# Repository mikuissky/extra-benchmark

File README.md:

# extra-benchmark
The extra benchmarks of paper "ADSAPlace:Alignment-Driven Simulated  Annealing for PCB Placement"

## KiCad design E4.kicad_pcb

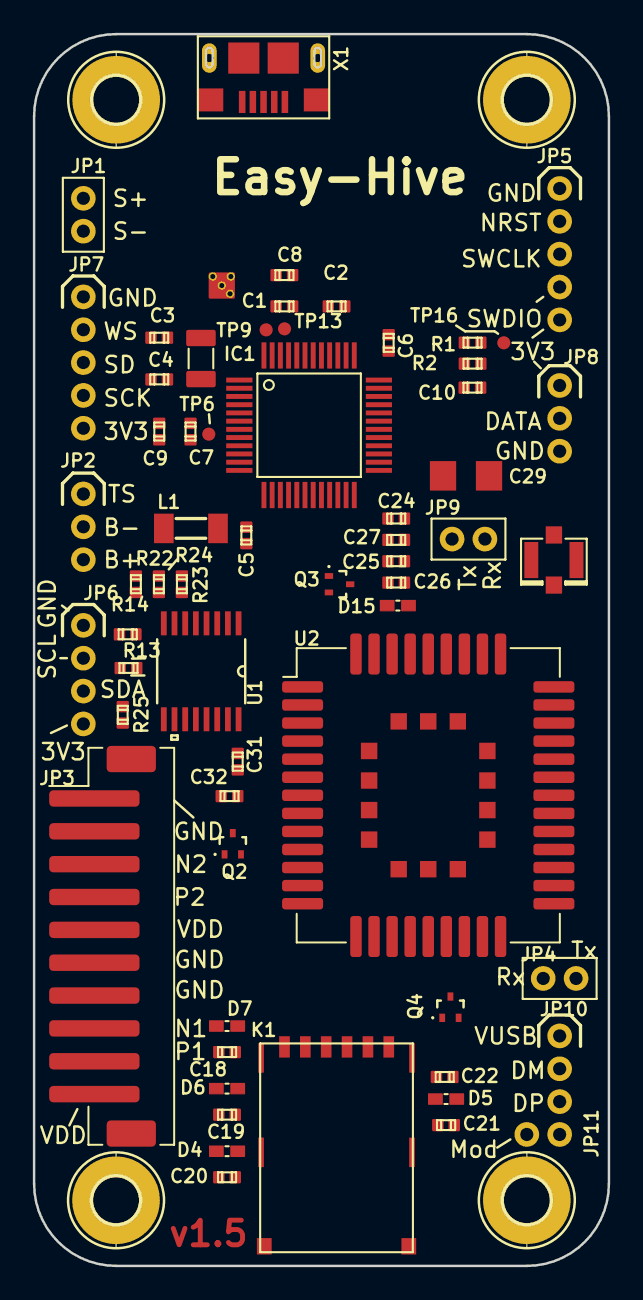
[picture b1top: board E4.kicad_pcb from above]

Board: 2 copper layers, 35.0 x 75.0 mm, 106 parts (0 on the bottom side), 82 nets, no tracks yet.

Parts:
C1, C5, C6, C7, C14, C15, C24, C28: 100n; C0402
C2, C11, C30, C31, C32: 1u; C0402
C3, C4, C26: 15p; C0402
C8, C9, C16, C17: 10u; C0402
C10: 100p; C0402
C12, C13, C23: 4u7; C0402
C18, C19, C20, C21: 47p; C0402
C22: 100nF; C0402
C25: 56p; C0402
C27: 10n; C0402
C29: 100u; 1206
D1, D2: MBR0520LT; SOD123
D4, D5, D6, D7, D8, D9, D10, D11, D12, D13, D14, D15: PESD0402-140; 0402-TVS
F1: 6V/0.5A; 1206
H1, H2, H3, H4: MOUNT-PAD-ROUND2.8; 2,8-PAD
IC1: ATSAMD21G; TQFP48
IC2: BQ2407X; VQFN16
IC3: ADS1232; TSSOP24
IC4: DS18B20U; UMAX8
IC5: XC6220B331; SOT25
IC7: TPS22919; sot-sc70-6
J1: U.FL
JP1: Solar; 1X02_2MM_klein
JP2: Battery; 1X03-2MM_klein
JP3: JST PH; JST_PH_B10B-PH-SM4-TB_1x10-1MP_P2.00mm_Vertical
JP4: UART_AUX; 1X02_2MM_klein
JP5: SWD; 1X05-2MM_klein
JP6: I2C; 1X04-2MM_klein
JP7: I2S; 1X05-2MM_klein
JP8: ext. DS18B20; 1X03-2MM_re_klein
JP9: UART_DBG; 1X02_2MM_klein
JP10: USB_BC66; 1X03-2MM_klein
JP11: USB_MODE; 1X02_2MM_klein
K1: 693043020611
L1, L2: SM-1206
P1: PKMCS; PKMCS_BUZZER
Q1: 32768 Hz; FC135
Q2, Q3, Q4: DTC123JET1G; SC75_SOT416
R1: 330; C0402
R2: 2k2; C0402
R3, R22, R23, R24: 0R; C0402
R4: 1k18; C0402
R5: 680R; C0402
R6, R10: 10K; C0402
R7, R8, R9: 22R; C0402
R13, R14: 2k; C0402
R15: NTC 103AT; C0402
R16: 4M7; C0402
R17: 10M; C0402
R18: 4k7; C0402
R25: 1M; C0402
TP6, TP9, TP10, TP11, TP13, TP16: TPTP08R; TP08R
U1: SN74AVC4T774PWG4; PW16
U2: BC66; Quectel_BC66
X1: USB_MICRO_SHIELD; USBMICRO

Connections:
+3V3: C1.1, C5.1, C6.1, C8.1, C10.1, C17.1, C24.1, C25.1, C26.1, C27.1, C29.1, C30.1, C31.2, D14.P$2, D15.P$2, IC1.17, IC1.36, IC1.44, IC3.1, IC3.19, IC3.20, IC4.8, IC5.5, IC7.1, JP5.5, JP6.4, JP7.5, JP8.3, L1.2, R2.2, R13.2, R14.2, R18.2, R24.1, R25.2, TP10.TP, U1.16, U2.42, U2.43
/3V3_LC: C15.1, IC3.16, IC3.18, IC7.4, JP3.5, JP3.10
/+1V8: C32.2, U1.15, U2.24
/ADS_A0: IC1.28, IC3.8
/AIN0: C28.1, IC1.3, R16.1, R17.2
/BC66_1V8_ENABLE: IC1.25, R25.1, U1.9
/BC66_PSM: IC1.8, Q4.1
/BC66_PWRON: IC1.19, Q2.1
/BC66_RI_1V8: U1.13, U2.20
/BC66_RI_3V3: IC1.23, U1.4
/BC66_RST: IC1.20, Q3.1
/BC66_RXD_1V8: U1.11, U2.18
/BC66_RXD_3V3: IC1.21, U1.6
/BC66_TXD_1V8: U1.12, U2.17
/BC66_TXD_3V3: IC1.22, U1.5
/BUZZER: IC1.41, P1.1
/DATA: IC1.10, IC3.24
/DS_DATA: IC1.39, IC4.1, JP8.2, R18.1, TP11.TP
/I2S_SCK: IC1.15, JP7.4
/I2S_SD: IC1.13, JP7.3
/I2S_WS: IC1.16, JP7.2
/LC_ON: IC1.29, IC7.3
/PB02: IC1.47, TP13.TP
/PB03: IC1.48, TP9.TP
/PB08: IC1.7, TP6.TP
/PDWN: IC1.12, IC3.22
/SAM_SCL: IC1.32, JP6.2, R14.1
/SAM_SDA: IC1.31, JP6.3, R13.1
/SCLK: IC1.11, IC3.23
/SWCLK: D12.P$2, IC1.45, JP5.3
/SWDIO: D13.P$2, IC1.46, JP5.4
/TEMP_EN: IC1.9, IC3.7
/USBN: D9.P$2, IC1.33, X1.2
/USBP: D8.P$2, IC1.34, X1.3
/VBAT: C12.1, IC2.2, IC2.3, JP2.3, R16.2
/VUSB: C23.1, D2.A, L2.2
/~RESET: C10.2, D11.P$2, IC1.40, JP5.2, R1.2, R2.1
GND: C1.2, C2.2, C3.2, C4.2, C5.2, C6.2, C7.2, C8.2, C9.2, C11.2, C12.2, C13.2, C15.2, C16.2, C17.2, C18.2, C19.2, C20.2, C21.2, C22.1, C23.2, C24.2, C25.2, C26.2, C27.2, C28.2, C29.2, C30.2, C31.1, C32.1, D4.P$2, D5.P$2, D6.P$2, D7.P$2, D8.P$1, D9.P$1, D10.P$1, D11.P$1, D12.P$1, D13.P$1, D14.P$1, D15.P$1, H1.B2,8, H2.B2,8, H3.B2,8, H4.B2,8, IC1.5, IC1.18, IC1.35, IC1.42, IC2.4, IC2.6, IC2.8, IC2.15, IC3.2, IC3.3, IC3.5, IC3.6, IC3.15, IC3.17, IC3.21, IC4.4, IC5.2, IC7.2, J1.P$1, J1.P$2, JP1.1, JP2.2, JP3.1, JP3.2, JP3.6, JP3.7, JP5.1, JP6.1, JP7.1, JP8.1, JP11.2, K1.C5, K1.Z1, K1.Z2, K1.Z3, K1.Z4, K1.Z5, K1.Z6, P1.2, Q2.2, Q3.2, Q4.2, R3.1, R4.1, R5.1, R15.1, R17.1, R22.1, R23.1, U1.10, U2.1, U2.10, U2.27, U2.34, U2.36, U2.37, U2.40, U2.41, X1.5, X1.S1, X1.S2, X1.S3, X1.S4, X1.S5, X1.S6
unnamed: C2.1, IC1.43
unnamed: C3.1, IC1.1, Q1.1
unnamed: C4.1, IC1.2, Q1.2
unnamed: C7.1, C9.1, IC1.6, L1.1
unnamed: C11.1, D1.C, D2.C, IC2.13
unnamed: C13.1, F1.1, IC2.5, IC2.10, IC2.11
unnamed: C14.1, IC3.9
unnamed: C14.2, IC3.10
unnamed: C18.1, D7.P$1, K1.C7, R8.2
unnamed: C19.1, D6.P$1, K1.C3, R9.2
unnamed: C20.1, D4.P$1, K1.C2, R7.2
unnamed: C21.1, C22.2, D5.P$1, K1.C1, R6.1, U2.14
unnamed: D1.A, JP1.2
unnamed: D10.P$2, L2.1, X1.1
unnamed: IC2.1, JP2.1, R15.2
unnamed: IC2.12, R4.2
unnamed: IC2.14, R3.2
unnamed: IC2.16, R5.2
unnamed: IC2.17, IC2.V1, IC2.V2, IC2.V3, IC2.V4
unnamed: IC3.11, JP3.9
unnamed: IC3.12, JP3.8
unnamed: IC3.13, JP3.3
unnamed: IC3.14, JP3.4
unnamed: J1.P$3, U2.35
unnamed: JP4.1, U2.29
unnamed: JP4.2, U2.28
unnamed: JP9.1, U2.39
unnamed: JP9.2, U2.38
unnamed: JP10.1, U2.49
unnamed: JP10.2, U2.51
unnamed: JP10.3, U2.50
unnamed: JP11.1, R10.2
unnamed: Q2.3, U2.7
unnamed: Q3.3, U2.15
unnamed: Q4.3, U2.19
unnamed: R1.1, TP16.TP
unnamed: R6.2, R8.1, U2.11
unnamed: R7.1, U2.12
unnamed: R9.1, U2.13
unnamed: R10.1, U2.47
unnamed: R22.2, U1.2
unnamed: R23.2, U1.7
unnamed: R24.2, U1.8
VCC: C16.1, F1.2, IC5.1, IC5.3

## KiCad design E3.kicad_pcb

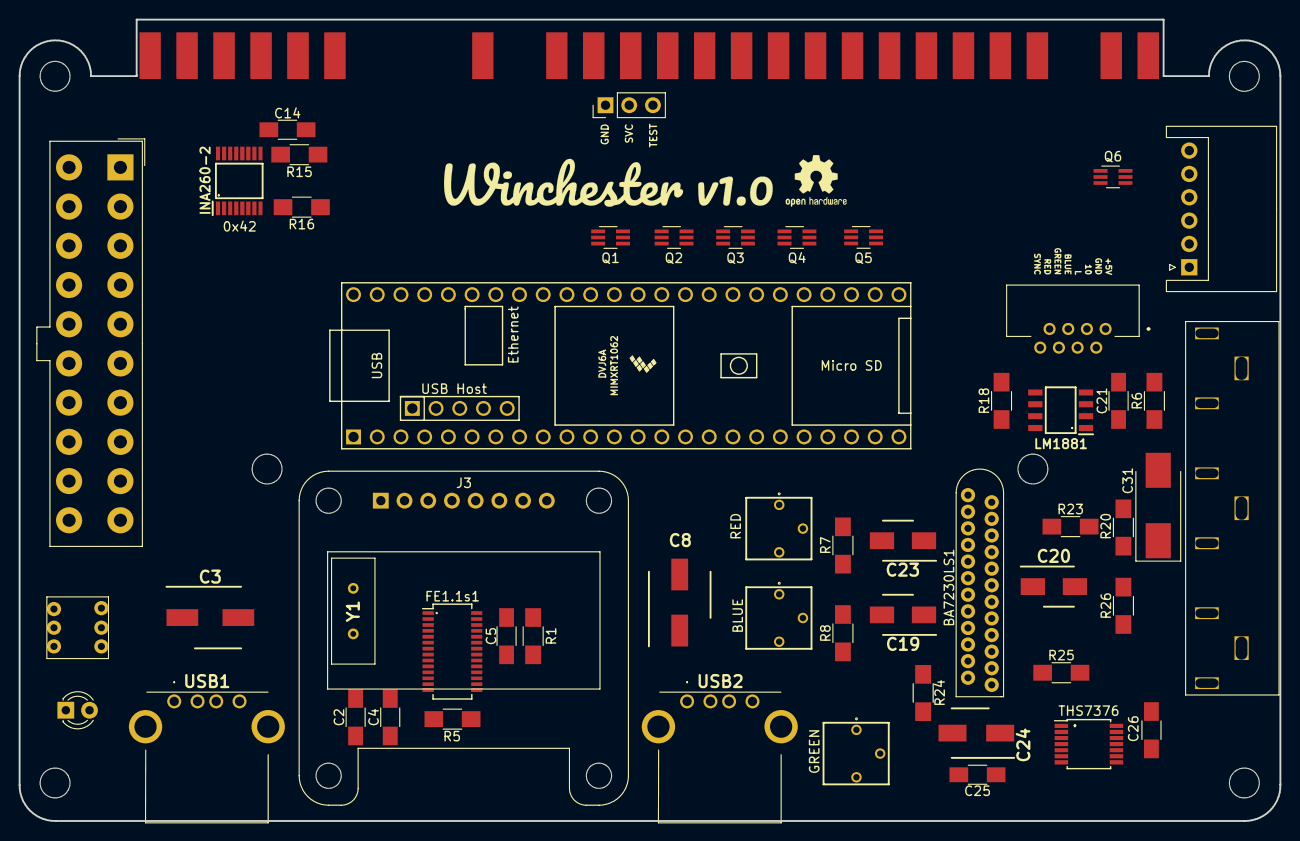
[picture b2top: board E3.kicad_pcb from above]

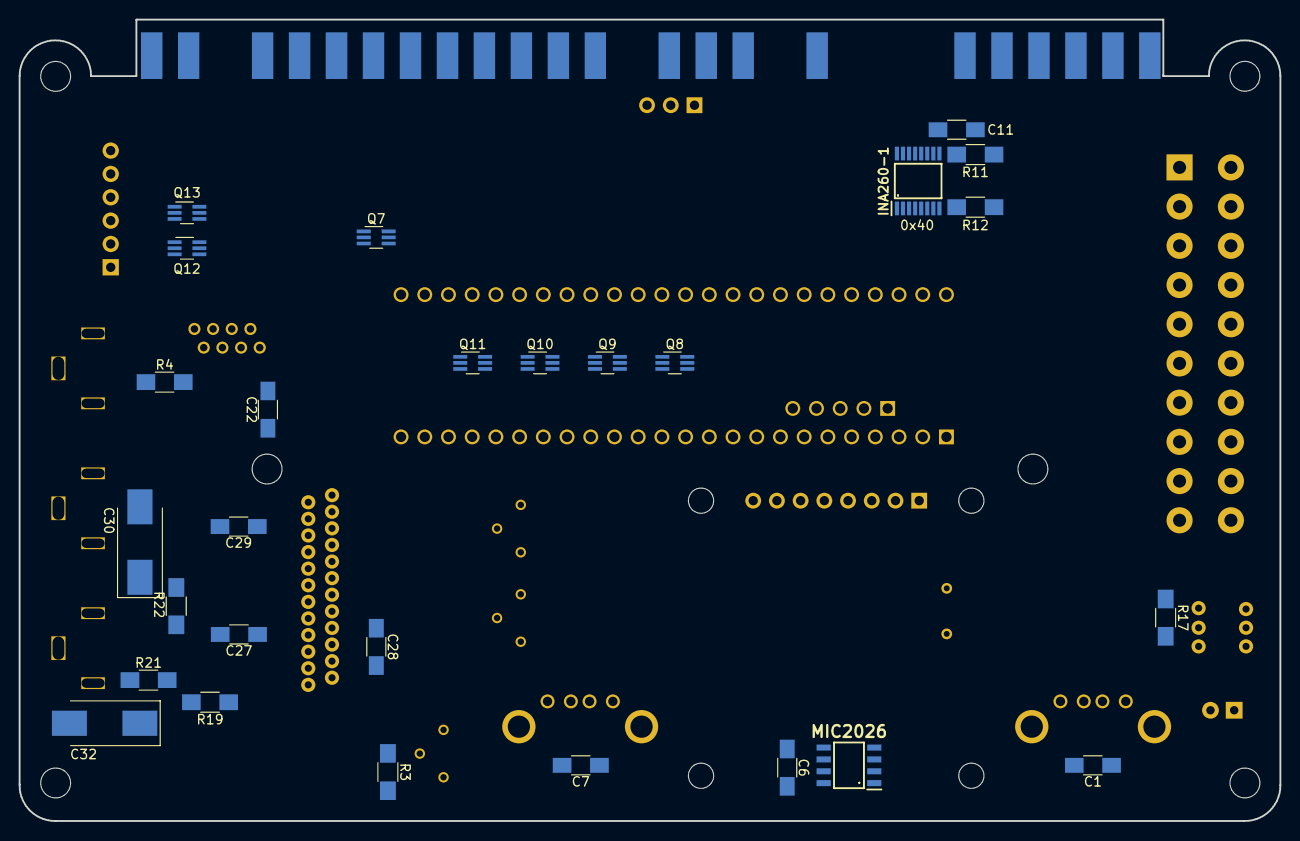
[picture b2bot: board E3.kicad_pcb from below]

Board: 2 copper layers, 135.1 x 85.8 mm, 89 parts (27 on the bottom side), 117 nets, no tracks yet.

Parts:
ATX1: ATX20; Molex_MiniFit-JR-5556-20A_2x10x4.20mm_Straight
BA7230LS1: BA7230LS; szip24
B_POT1: R_POT_TRIM; 3362P_1
C1, C6, C7, C21, C22, C26, C27, C28, C29: 0.1uF; C_1206_HandSoldering
C2, C4, C5: 10uF; C_1206_HandSoldering
C3, C8: 220uF; EEE-1CA221XP
C11, C14: 1uF; C_1206_HandSoldering
C19, C20, C23: 1uF; EEE1HA010SR
C24: 10uF; EEE-1EA100SR
C25: 0.047uF; C_1206_HandSoldering
C30, C31, C32: 220uF; CP_Tantalum_Case-D_EIA-7343-31_Hand
COMPONENT1: PJRAN
D1: LED; LED_D3.0mm
FE1.1s1: FE1.1s; SSOP-28_3.9x9.9mm_Pitch0.635mm
G_POT1: R_POT_TRIM; 3362P_1
H1, H2, H3, H4, H5, H6: MountingHole; MountingHole_3.2mm_M3
INA260-1, INA260-2: INA260
J1: Conn_01x03_Female; Pin_Header_Straight_1x03_Pitch2.54mm
J2: SLW8R-5C7LF; SLW8R5C7LF
J3: SSD1306 OLED; Adafruit_SSD1306
KICK1: JST-XH; JST_XH_S06B-XH-A_06x2.50mm_Angled
L1: Logo; v1
LM1881: LM1881
LOGO1: Logo_Open_Hardware_Small; OSHW-Logo2_7.3x6mm_SilkScreen
MIC2026: MIC2026-2YM; SOIC127P599X173-8N
POWER1: SW_DPDT_x2; POWER_SW
Q1, Q2, Q3, Q4, Q5, Q6, Q7, Q8, Q9, Q10, Q11, Q12, Q13: MUN5230DW1T1G; SOT-363_SC-70-6_Handsoldering
R1, R11, R12, R15, R16: 10k; R_1206_HandSoldering
R3, R6, R7, R8: 390ohm; R_1206_HandSoldering
R4: 1Kohm; R_1206_HandSoldering
R5: 2.7k; R_1206_HandSoldering
R17: 330; R_1206_HandSoldering
R18: 680k; R_1206_HandSoldering
R19: 82ohm; R_1206_HandSoldering
R20: 56ohm; R_1206_HandSoldering
R21: 91ohm; R_1206_HandSoldering
R22: 75ohm; R_1206_HandSoldering
R23, R24, R25: 3.6Mohm; R_1206_HandSoldering
R26: 200ohm; R_1206_HandSoldering
R_POT1: R_POT_TRIM; 3362P_1
THS7376: THS7376; TSSOP-14_4.4x5mm_Pitch0.65mm
U1: Jamma; JAMMA56HALF
U7: Teensy4.1; Teensy41
USB1, USB2: USB_A; 875201010BLF
Y1: ECS120; ECS120184XCKM

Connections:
+3V3: ATX1.11, R1.1
+5V: ATX1.19, ATX1.20, BA7230LS1.24, C5.2, C6.2, C11.1, C14.1, C24.1, C25.1, C26.1, FE1.1s1.20, INA260-1.10, INA260-2.10, J2.1, J3.7, LM1881.8, MIC2026.7, R11.1, R12.1, R15.1, R16.1, R23.1, R24.1, R25.1, THS7376.10, U7.48
-5V: ATX1.18, U1.5, U1.E
/10: J2.3, U1.10
/+5VA: ATX1.4, ATX1.6, INA260-2.1, INA260-2.2, INA260-2.3, INA260-2.12
/+5VB: INA260-2.14, INA260-2.15, INA260-2.16, U1.3, U1.4, U1.C, U1.D
/+12VA: ATX1.10, INA260-1.1, INA260-1.2, INA260-1.3, INA260-1.12
/+12VB: INA260-1.14, INA260-1.15, INA260-1.16, U1.6, U1.F
/B: B_POT1.1, U1.13
/B-Y: C28.2, R24.2, THS7376.3
/BLUE: B_POT1.2, C19.2, J2.5, R8.2
/BYPASS: THS7376.9, U7.17
/CH1: C30.2, COMPONENT1.6, COMPONENT1.7
/CH2: C31.2, COMPONENT1.8, COMPONENT1.9
/CH3: C32.2, COMPONENT1.4, COMPONENT1.5
/COIN_P1: Q1.3, U1.16
/COIN_P2: Q8.6, U1.T
/CSYNC: J2.8, LM1881.1, R26.2
/DM: FE1.1s1.15, U7.56
/DM1: FE1.1s1.10, USB1.2
/DM2: FE1.1s1.8, USB2.2
/DP: FE1.1s1.16, U7.57
/DP1: FE1.1s1.11, USB1.3
/DP2: FE1.1s1.9, USB2.3
/ENP: FE1.1s1.25, MIC2026.1, MIC2026.4
/G: G_POT1.1, U1.N
/GREEN: C20.2, G_POT1.2, J2.6, R3.1
/L: J2.4, U1.L
/OVCJ: FE1.1s1.26, MIC2026.2, MIC2026.3, R1.2
/P1_B1: Q4.3, U1.22
/P1_B1_29: Q4.5, U7.29
/P1_B2: Q4.6, U1.23
/P1_B2_30: Q4.2, U7.30
/P1_B3: Q5.3, U1.24
/P1_B3_27: Q5.5, U7.27
/P1_B4: KICK1.1, Q12.3
/P1_B4_23: Q12.5, U7.23
/P1_B4_28: Q5.2, U7.28
/P1_B4_N: Q5.6, U1.25
/P1_B5: KICK1.3, Q13.3
/P1_B5_21: Q13.5, U7.21
/P1_B6: KICK1.5, Q6.6
/P1_B6_19: Q6.2, U7.19
/P1_COIN_37: Q1.5, U7.37
/P1_DOWN: Q2.6, U1.19
/P1_DOWN_36: Q2.2, U7.36
/P1_LEFT: Q3.3, U1.20
/P1_LEFT_32: Q3.5, U7.32
/P1_RIGHT: Q3.6, U1.21
/P1_RIGHT_33: Q3.2, U7.33
/P1_START: Q1.6, U1.17
/P1_START_38: Q1.2, U7.38
/P1_UP: Q2.3, U1.18
/P1_UP_35: Q2.5, U7.35
/P2_B1: Q11.6, U1.Z
/P2_B1_18: Q11.2, U7.18
/P2_B2: Q11.3, U1._a
/P2_B2_14: Q11.5, U7.14
/P2_B3: Q7.6, U1._b
/P2_B3_25: Q7.2, U7.25
/P2_B4: KICK1.2, Q12.6
/P2_B4_24: Q12.2, U7.24
/P2_B4_26: Q7.5, U7.26
/P2_B4_N: Q7.3, U1._c
/P2_B5: KICK1.4, Q13.6
/P2_B5_22: Q13.2, U7.22
/P2_B6: KICK1.6, Q6.3
/P2_B6_20: Q6.5, U7.20
/P2_COIN_9: Q8.2, U7.9
/P2_DOWN: Q9.3, U1.W
/P2_DOWN_10: Q9.5, U7.10
/P2_LEFT: Q10.6, U1.X
/P2_LEFT_13: Q10.2, U7.13
/P2_RIGHT: Q10.3, U1.Y
/P2_RIGHT_12: Q10.5, U7.12
/P2_START: Q8.3, U1.U
/P2_START_8: Q8.5, U7.8
/P2_UP: Q9.6, U1.V
/P2_UP_11: Q9.2, U7.11
/R: R_POT1.1, U1.12
/R-Y: C27.2, R25.2, THS7376.4
/RED: C23.2, J2.7, R7.2, R_POT1.2
/S: R4.2, U1.P
/SCL: INA260-1.9, INA260-2.9, J3.2, R11.2, R15.2, U7.41
/SDA: INA260-1.5, INA260-1.8, INA260-2.8, J3.1, R12.2, R16.2, U7.40
/SERVICE: J1.2, U1.R
/SYNC: C21.2, R4.1, R6.2
/TEST: J1.3, U1.15
/USBA5V: C1.1, C3.1, MIC2026.8, USB1.1
/USBB5V: C7.1, C8.1, MIC2026.5, USB2.1
/USBVCC: FE1.1s1.18, U7.55
/Y: C29.2, R23.2, THS7376.2
GND: ATX1.3, ATX1.5, ATX1.7, ATX1.13, ATX1.16, ATX1.17, BA7230LS1.19, B_POT1.3, C1.2, C2.1, C3.2, C4.1, C5.1, C6.1, C7.2, C8.2, C11.2, C14.2, C22.1, C24.2, C25.2, C26.2, COMPONENT1.1, COMPONENT1.2, COMPONENT1.3, D1.1, FE1.1s1.1, G_POT1.3, INA260-1.4, INA260-1.6, INA260-1.11, INA260-2.4, INA260-2.5, INA260-2.6, INA260-2.11, J1.1, J2.2, J3.8, LM1881.4, MIC2026.6, Q1.1, Q1.4, Q2.1, Q2.4, Q3.1, Q3.4, Q4.1, Q4.4, Q5.1, Q5.4, Q6.1, Q6.4, Q7.1, Q7.4, Q8.1, Q8.4, Q9.1, Q9.4, Q10.1, Q10.4, Q11.1, Q11.4, Q12.1, Q12.4, Q13.1, Q13.4, R3.2, R5.2, R6.1, R7.1, R8.1, R18.1, R_POT1.3, THS7376.5, THS7376.6, U1.1, U1.2, U1.14, U1.27, U1.28, U1.A, U1.B, U1._e, U1._f, U7.1, U7.34, U7.47, U7.58, U7.59, USB1.4, USB2.4
unnamed: ATX1.8, R17.1
unnamed: ATX1.14, POWER1.3
unnamed: ATX1.15, POWER1.1
unnamed: BA7230LS1.13, C23.1
unnamed: BA7230LS1.14, C20.1
unnamed: BA7230LS1.15, C19.1
unnamed: BA7230LS1.16, C29.1
unnamed: BA7230LS1.17, C28.1
unnamed: BA7230LS1.18, C27.1
unnamed: C2.2, FE1.1s1.12, FE1.1s1.28
unnamed: C4.2, FE1.1s1.13, FE1.1s1.19, FE1.1s1.21
unnamed: C21.1, LM1881.2
unnamed: C22.2, LM1881.6, R18.2
unnamed: C30.1, R22.1
unnamed: C31.1, R20.1
unnamed: C32.1, R21.1
unnamed: D1.2, R17.2
unnamed: FE1.1s1.2, Y1.2
unnamed: FE1.1s1.3, Y1.1
unnamed: FE1.1s1.14, R5.1
unnamed: R19.1, R22.2, R26.1
unnamed: R19.2, THS7376.13
unnamed: R20.2, THS7376.12
unnamed: R21.2, THS7376.11

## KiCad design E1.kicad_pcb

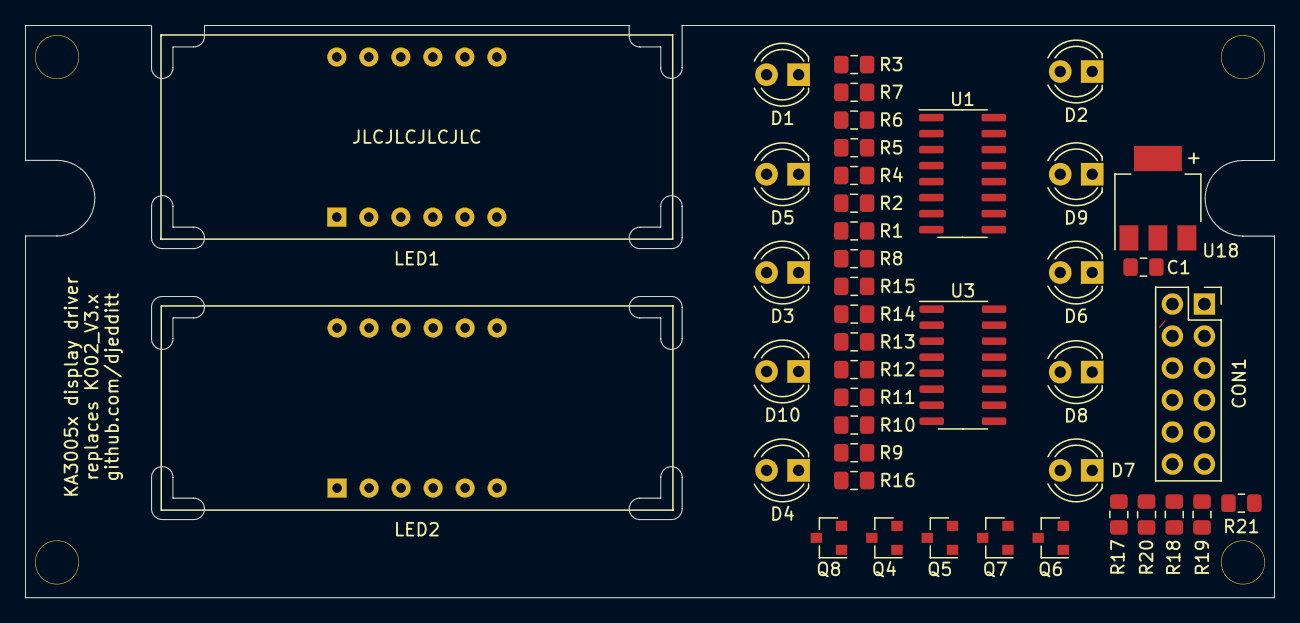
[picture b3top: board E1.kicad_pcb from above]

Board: 2 copper layers, 99.1 x 45.4 mm, 43 parts (0 on the bottom side), 54 nets, no tracks yet.

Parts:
C1: 22uF; C_0805_2012Metric_Pad1.15x1.40mm_HandSolder
CON1: Conn_02x06_Odd_Even; PinSocket_2x06_P2.54mm_Vertical
D1, D2, D3, D4, D5, D6, D7, D8, D9, D10: LED; LED_D4.0mm
LED1, LED2: NFD-4042Ax
Q4, Q5, Q6, Q7, Q8: MMBT3904; SOT-23
R1, R2, R3, R4, R5, R6, R7, R8, R9, R10, R11, R12, R13, R14, R15, R16: 330; R_0805_2012Metric_Pad1.15x1.40mm_HandSolder
R17, R18, R19, R20, R21: 1K; R_0805_2012Metric_Pad1.15x1.40mm_HandSolder
U1, U3: 74HC595; SOIC-16_3.9x9.9mm_P1.27mm
U18: AZ1117-3.3; SOT-223

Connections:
+3V3: C1.2, U1.10, U1.16, U3.10, U3.16, U18.2, U18.4
GND: C1.1, CON1.2, Q4.2, Q5.2, Q6.2, Q7.2, Q8.2, U1.8, U1.13, U3.8, U3.13, U18.1
unnamed: CON1.1, U18.3
unnamed: CON1.3, U1.12, U3.12
unnamed: CON1.4, U1.11, U3.11
unnamed: CON1.6, U3.14
unnamed: CON1.8, R17.1
unnamed: CON1.9, R21.1
unnamed: CON1.10, R20.1
unnamed: CON1.11, R19.1
unnamed: CON1.12, R18.1
unnamed: D1.1, D2.1, D3.1, D4.1, D5.1, D6.1, D7.1, D8.1, D9.1, D10.1, Q7.3
unnamed: D1.2, LED1.7, R3.1
unnamed: D2.2, LED1.11, R1.1
unnamed: D3.2, LED1.5, R8.1
unnamed: D4.2, LED2.5, R16.1
unnamed: D5.2, LED1.2, R5.1
unnamed: D6.2, LED1.4, R7.1
unnamed: D7.2, LED2.4, R15.1
unnamed: D8.2, LED2.3, R14.1
unnamed: D9.2, LED2.7, R9.1
unnamed: D10.2, LED2.1, R12.1
unnamed: LED1.1, R4.1
unnamed: LED1.3, R6.1
unnamed: LED1.6, LED2.6, Q5.3
unnamed: LED1.8, LED2.8, Q4.3
unnamed: LED1.9, LED2.9, Q6.3
unnamed: LED1.10, R2.1
unnamed: LED1.12, LED2.12, Q8.3
unnamed: LED2.2, R13.1
unnamed: LED2.10, R10.1
unnamed: LED2.11, R11.1
unnamed: Q4.1, R19.2
unnamed: Q5.1, R18.2
unnamed: Q6.1, R17.2
unnamed: Q7.1, R20.2
unnamed: Q8.1, R21.2
unnamed: R1.2, U1.7
unnamed: R2.2, U1.6
unnamed: R3.2, U1.5
unnamed: R4.2, U1.4
unnamed: R5.2, U1.3
unnamed: R6.2, U1.2
unnamed: R7.2, U1.1
unnamed: R8.2, U1.15
unnamed: R9.2, U3.7
unnamed: R10.2, U3.6
unnamed: R11.2, U3.5
unnamed: R12.2, U3.4
unnamed: R13.2, U3.3
unnamed: R14.2, U3.2
unnamed: R15.2, U3.1
unnamed: R16.2, U3.15
unnamed: U1.14, U3.9

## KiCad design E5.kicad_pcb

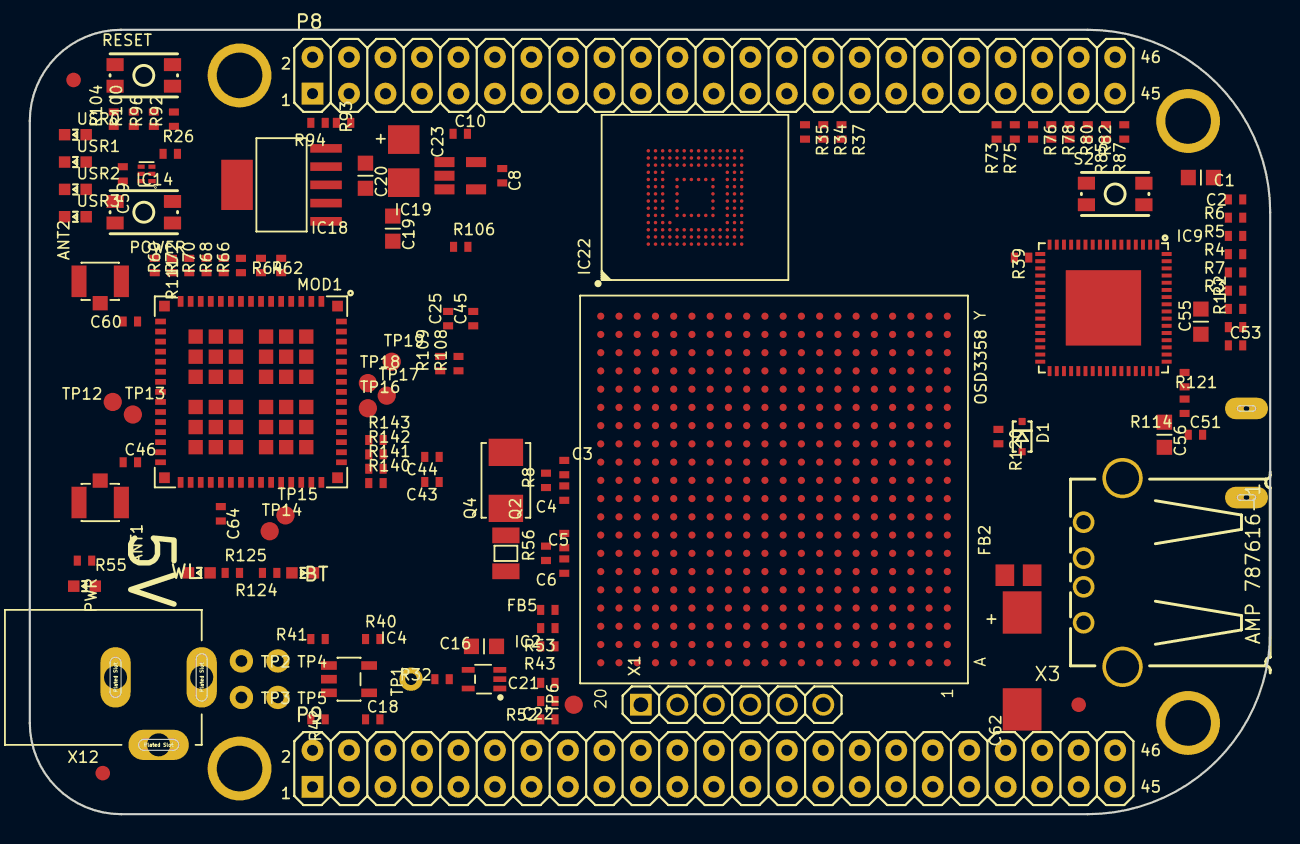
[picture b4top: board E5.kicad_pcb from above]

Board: 4 copper layers, 86.4 x 54.6 mm, 275 parts (0 on the bottom side), 262 nets, no tracks yet.

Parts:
ANT1, ANT2: U.FL-R-SMT-1(10); U.FL-R-SMT-1
BT: LTST-C191TBKT; 0603-LED
C1: 10uF,10V; C0603K
C2, C13, C15, C17, C18, C21, C22, C24, C25, C43, C44, C45, C47, C48, C49, C50, C51, C52, C53, C58, C59, C63, C69: .1uF, 6.3V; C0402K
C3, C4, C5, C6: 18pF, 50V; C0402K
C7: 4.7uF, 6.3V; C0805K
C8, C10: 1uF; C0402K
C9, C12, C14: 2.2uF, 6.3V; C0805K
C11, C23: 47uF DNP; CT3528
C16, C54, C55, C56, C57: 2.2uF, 6.3V; C0603K
C19, C20, C61: 10uF, 6.3V; C0603K
C27, C28, C29, C30, C31, C32, C33, C34, C35, C36, C37, C38, C39, C40, C41, C42: 47pF, 6.3V; C0402K
C46, C60: 10pF; C0402K
C62: 220uF 6.3V; D_7343-31W
C64: 1uF, 6.3V; C0402K
D1: RB751V40,115; SOD323(NXP)REFLOW
D2: STPS140A DNP; DIODE_SMA
D3, D4: STPS140A; DIODE_SMA
D8: BAT54C; SOT23
F1: 1206L025YR; SM-1206
FB1: 220 Ohm 800mA; 0805-RESISTOR
FB2: 2.5k Ohm (BLM18BD252SN1D); 0805-RESISTOR
FB3: 150 Ohm 800mA; 0805-RESISTOR
FB4: 0.1 Ohm, 0805; 0805-RESISTOR
FB5, FB6, FB7: 1k BLM15AG102SN1D; R0402
FUD1, FUD2, FUD3, FUD4, FUD5, FUD6: FIDUCIAL; FIDUCIAL_40MIL
IC1: OSD3358
IC2: SN74LVC1G07DCK; SC70(TI-DCK)
IC3: SN74LVC1G06DCK; SC70(TI-DCK)
IC4: 24LC32AT-I/OT; SOT23-5(MICROCHIP)
IC5: TLVH431 (SOT-23-3); DBZ_R-PDSO-G3
IC6: DNP TLVH431 (SOT-23-3); DBZ_R-PDSO-G3
IC7, IC8: IP4283CZ10-TBR; SOT1176-1(NXP)
IC9: TDA19988BHN/C1,557; SOT804-4(NXP)
IC10, IC11: TXS0108ERGYR; R-PVQFN-N20(TI)
IC12: TPS2051BDGN; MSOP-POWER.PAD-8(TI)
IC13: SN74AUC1G74; SM8-8(TI)
IC14, IC15: TPD4S012DRY; SON-6(TI)-DRY
IC17: SN74LVC2G241DCUR; VSSOP8(TI)
IC18: TL1963ADCQR; SOT-223(DCQ_R-PDSO-G6_TI)
IC19: AP2112K-1.8TRG1 3.3V; SOT23-5
IC22: MICRON_EMMC_153
MGT1, MGT2, MGT3, MGT4: MOUNTING_HOLE
MOD1: WL1835MODGBMOCT; MOC-100(TI)
OSC1: ASDMB-24.576MHZ-LC-T; OSCILLATOR-2.5X2.0-BBB
OSC2: NZ2520SB-32.768KHZ-NSA3534C; NZ2520S
P2: JTAG
P8, P9: TH-2X23
POWER: MINI_PUSHBUTTON
PWR: LTST-C191TBKT; 0603-LED
Q2: 32.768kHz; CRYSTAL_3.2X1.5
Q4: 24 MHz; CRYSTAL_5X3.2MM
R1, R2, R3, R4, R5, R6, R7, R12, R13, R16, R18, R19, R20, R23, R24, R25, R28, R30, R31, R32, R33, R40, R119, R121: 10k, 1%; R0402
R8: 1M, 1%; R0402
R10, R11: 150k; R0402
R14, R26, R27, R29, R35, R36, R37, R38, R39, R54, R114, R122: 0, 1%; R0402
R17: .1, 0805; R0805
R21, R22, R43, R52, R53, R55: 4.75k, 1%; R0402
R34: 22; R0402
R41, R42, R115, R118: 1.5k, 1%; R0402
R44: 499; R0402
R45, R49: DNP; R0402
R46: 10k 1%; R0402
R47: 40.2k 1%; R0402
R48: DNP 499; R0402
R50: DNP 10k 1%; R0402
R51: DNP 40.2k 1%; R0402
R56: DNP 1M, 1%; R0402
R57, R58, R61, R63, R65, R67, R69, R71, R73, R75, R76, R78, R80, R82, R85, R87, R123: 100k, 1%; R0402
R60, R62, R64, R66, R68, R70, R72, R140, R141, R142, R143: 33, 5%; R0402
R86, R126, R127, R128, R129, R130, R131, R134, R135, R136: 33, 5%; R0603
R88: 100, 1%; R0402
R89, R90, R92, R96, R100, R104, R124, R125: 1k; R0402
R91: 0 DNP; R0402
R93: 7.15k; R0402
R94: 4.12k; R0402
R95: 1M; R0402
R97, R108, R109: DNP 1k; R0402
R98, R99, R101, R102, R103, R105: 10k; R0402
R106: 1.5k; R0402
R110: 33; R0402
R111: DNP 10k; R0402
R120: 27k, 1%; R0402
RESET: MINI_PUSHBUTTON
S2: MINI_PUSHBUTTON
T1: MMBT2907; SOT23-BEC
T2: DNP MMBT2907; SOT23-BEC
T3, T4: BSS138W-7-F; SOT-323(DIODES)
TP1, TP2, TP3, TP4, TP5: TESTPAD/W_HOLE_1X1; TESTPAD_W_HOLE_1X1
TP6, TP12, TP13, TP14, TP15, TP16, TP17, TP18, TP19, TP23: PTR1B1,27; B1,27
USR0, USR1, USR2, USR3: LTST-C191TBKT; 0603-LED
WL: LTST-C191TBKT; 0603-LED
X1: TH-1X6
X2: SCHA5B0200
X3: USB_HOST_HORIZONTAL_W_CHASSIS_GND
X4: 10118192-0001LF; 10118192-0001LF(MICRO-USB-B-AMPHENOL-FCI)
X5: 10118241-001RLF; HDMI-TYPE-D-10118241
X12: PJ-102B_POWER_CON

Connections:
3.3V-WIFI: C8.1, C11.+, C24.1, C25.1, C43.1, C64.1, IC10.2, IC11.2, IC19.5, MOD1.38, OSC2.4, R90.1, R98.1, R99.1, R101.1, R102.1, R103.1, R105.1, R111.1
5V_IN: C19.1, D8.3, FB1.2, IC18.2, R95.1
12MHZ: FB6.2, IC9.27
12M_LOOP: IC13.2, IC13.3
32.768KHZ: MOD1.36, OSC2.3, R91.2
AGND: IC1.A6, IC1.A9, IC1.E8, P9.34
AIN0: IC1.B6, P9.39
AIN1: IC1.C7, P9.40
AIN2: IC1.B7, P9.37
AIN3: IC1.A7, P9.38
AIN4: IC1.C8, P9.33
AIN5: IC1.B8, P9.36
AIN6: IC1.A8, P9.35
AIN7: IC1.C9, R21.2, R22.1
ALT.BT.EN: IC10.10, IC11.10, R106.1, R131.1
ALT.BUFF.OE: IC10.15, R126.2
ALT.WL.CLK: IC11.18, R136.2
ALT.WL.CMD: IC11.17, R135.2
ALT.WL.D0: IC10.18, R129.2
ALT.WL.D1: IC10.17, R128.2
ALT.WL.D2: IC10.16, R127.2
ALT.WL.D3: C10.1, C20.1, C23.+, C44.1, C45.1, C61.1, C63.1, IC10.19, IC11.19, IC18.4, IC19.1, IC19.3, MOD1.46, MOD1.47, R93.1, R124.2, R125.2
ALT.WL.EN: IC11.12, R134.2
ALT.WL.IRQ: IC10.20, R130.2
BAT_TEMP: IC1.W1, TP4.P$1
BAT_VOLT: IC1.Y1, TP3.P$1
BT_EN: IC11.4, MOD1.41, R11.1, T4.G
BT_EN.SIP: IC1.K17, R135.1
BT_HCI_CTS: IC11.8, R141.2
BT_HCI_CTS.SIP: IC1.M17, IC11.15, R108.1
BT_HCI_RTS: IC11.6, R140.2
BT_HCI_RTS.SIP: IC1.M18, IC11.13, R109.1
BT_HCI_RX: IC11.1, R143.2
BT_HCI_RX.SIP: IC1.L17, IC11.14
BT_HCI_TX: IC11.7, R142.2
BT_HCI_TX.SIP: IC1.L16, IC11.20
CEC: D1.C, IC9.30, X5.15
CGND: T3.D, WL.K
CLKOUT2: FB7.1, IC11.16, P2.18, P9.41, R14.1
DVI_5V: F1.1, R115.1, R118.1, X5.19
EHRPWM1A: IC1.U14, P9.14
EHRPWM1B: IC1.T14, P9.16
EHRPWM2A: IC1.U10, P8.19
EHRPWM2B: IC1.T10, P8.13
EMMC_RSTN: IC22.K5, R29.1, R33.1
EXT_SWING: IC9.34, R119.1
GND: ANT1.GND1, ANT1.GND2, ANT2.GND1, ANT2.GND2, C1.2, C2.2, C7.2, C8.2, C9.2, C10.2, C11.-, C12.2, C13.2, C14.2, C15.2, C16.2, C17.2, C18.2, C19.2, C20.2, C21.2, C22.2, C23.-, C24.2, C25.2, C27.2, C28.2, C29.2, C30.2, C31.2, C32.2, C33.2, C34.2, C35.2, C36.2, C37.2, C38.2, C39.2, C40.2, C41.2, C42.2, C43.2, C44.2, C45.2, C47.2, C48.2, C49.2, C50.2, C51.2, C52.2, C53.2, C54.2, C55.2, C56.2, C57.2, C58.2, C59.2, C61.2, C62.-, C63.2, C64.2, C69.2, D8.2, IC1.A1, IC1.A18, IC1.E19, IC1.E20, IC1.F8, IC1.F19, IC1.G8, IC1.G9, IC1.G11, IC1.G12, IC1.G19, IC1.H6, IC1.H7, IC1.H8, IC1.H9, IC1.H10, IC1.H12, IC1.H19, IC1.J6, IC1.J7, IC1.J8, IC1.J9, IC1.J10, IC1.J11, IC1.J19, IC1.J20, IC1.K7, IC1.K9, IC1.K10, IC1.K11, IC1.K19, IC1.L10, IC1.L11, IC1.L12, IC1.L13, IC1.L19, IC1.M6, IC1.M7, IC1.M8, IC1.M9, IC1.M10, IC1.M12, IC1.M14, IC1.M19, IC1.N7, IC1.N10, IC1.N11, IC1.N14, IC1.N19, IC1.N20, IC1.P19, IC1.P20, IC1.R19, IC1.R20, IC1.T19, IC1.T20, IC1.U19, IC1.V1, IC1.V18, IC1.V19, IC1.W2, IC1.W3, IC1.W5, IC1.W6, IC1.W7, IC1.W8, IC1.W9, IC1.W10, IC1.W11, IC1.W12, IC1.W13, IC1.W14, IC1.W15, IC1.W16, IC1.W17, IC1.W18, IC1.W19, IC1.W20, IC1.Y7, IC1.Y10, IC1.Y12, IC1.Y15, IC1.Y18, IC2.3, IC3.3, IC4.2, IC7.3, IC7.8, IC8.3, IC8.8, IC9.8, IC9.9, IC9.16, IC9.17, IC9.18, IC9.19, IC9.53, IC9.54, IC9.61, IC9.62, IC9.63, IC9.65, IC10.11, IC10.TP, IC11.11, IC11.TP, IC12.1, IC12.9, IC13.4, IC14.4, IC15.4, IC17.1, IC17.4, IC18.3, IC18.6, IC19.2, IC22.C4, IC22.E7, IC22.G5, IC22.H10, IC22.K8, IC22.N2, IC22.N5, IC22.P4, IC22.P6, MOD1.1, MOD1.7, MOD1.9, MOD1.15, MOD1.16, MOD1.17, MOD1.19, MOD1.20, MOD1.23, MOD1.24, MOD1.28, MOD1.29, MOD1.30, MOD1.31, MOD1.33, MOD1.34, MOD1.35, MOD1.37, MOD1.39, MOD1.44, MOD1.45, MOD1.48, MOD1.49, MOD1.54, MOD1.55, MOD1.59, MOD1.61, MOD1.63, MOD1.64, MOD1.G1, MOD1.G2, MOD1.G3, MOD1.G4, MOD1.G5, MOD1.G6, MOD1.G7, MOD1.G8, MOD1.G9, MOD1.G10, MOD1.G11, MOD1.G12, MOD1.G13, MOD1.G14, MOD1.G15, MOD1.G16, MOD1.G17, MOD1.G18, MOD1.G19, MOD1.G20, MOD1.G21, MOD1.G22, MOD1.G23, MOD1.G24, MOD1.G25, MOD1.G26, MOD1.G27, MOD1.G28, MOD1.G29, MOD1.G30, MOD1.G31, MOD1.G32, MOD1.G33, MOD1.G34, MOD1.G35, MOD1.G36, OSC1.2, OSC2.2, P2.4, P2.8, P2.10, P2.12, P2.16, P2.20, P8.1, P8.2, P9.1, P9.2, P9.43, P9.44, P9.45, P9.46, POWER.1, POWER.2, R10.2, R11.2, R17.1, R19.2, R22.2, R24.1, R27.2, R52.2, R55.1, R57.1, R61.1, R63.1, R65.1, R67.1, R69.1, R71.1, R73.1, R75.1, R85.1, R87.1, R94.2, R95.2, R106.2, R108.2, R109.2, R114.1, R119.2, R123.2, RESET.1, RESET.2, S2.3, S2.4, T3.S, T4.S, TP5.P$1, USR0.K, USR1.K, USR2.K, USR3.K, X1.1, X2.6, X2.GND, X3.4, X4.GND, X5.4, X5.7, X5.10, X5.13, X5.16, X12.OUT
GPIO0_7: P9.42, R36.1, R38.1
GPIO0_26: IC1.T11, P8.14
GPIO0_27: IC1.U12, P8.17
GPIO1_12: IC1.T12, P8.12
GPIO1_13: IC1.R12, P8.11
GPIO1_14: IC1.V13, P8.16
GPIO1_15: IC1.U13, P8.15
GPIO1_16: P9.15, R54.1
GPIO1_16.SIP: IC1.R13, R54.2
GPIO1_17: IC1.V14, P9.23
GPIO1_28: IC1.U18, P9.12
GPIO1_29: IC1.V6, P8.26
GPIO2_1: IC1.V12, P8.18
GPIO3_19: IC1.C13, P9.27
GPIO3_21: IC1.A14, P9.25, R110.2
HDMI.DSCL: IC9.33, R115.2, X5.17
HDMI.DSDA: IC9.32, R118.2, X5.18
HDMICLK_DIS#: IC1.V17, OSC1.1
HDMI_1V8: C50.1, C51.1, C52.1, C53.1, C54.1, C55.1, C56.1, C57.1, FB2.2, IC9.5, IC9.14, IC9.29, IC9.35, IC9.36, IC9.41, IC9.46, IC9.47, IC9.48, IC9.55
HDMI_INT: IC1.U16, IC9.50, R121.2
HPD: IC9.31, X5.1
I2C0_SCL: IC1.C16, IC1.C20, IC4.1, IC9.52, R41.2
I2C0_SDA: IC1.C17, IC1.C19, IC4.3, IC9.51, R42.2
I2C1_SCL: IC1.A16, P9.17
I2C1_SDA: IC1.B16, P9.18
I2C2_SCL: IC1.D17, P9.19
I2C2_SDA: IC1.D18, P9.20
JTAG_EMU0: IC1.C14, P2.13, R43.2
JTAG_EMU1: IC1.B14, P2.14, R53.2
JTAG_TCK: IC1.A12, P2.9, P2.11
JTAG_TDI: IC1.B11, P2.3
JTAG_TDO: IC1.A11, P2.7
JTAG_TMS: IC1.C11, P2.1
JTAG_TRSTN: IC1.B10, P2.2, R52.1
LCD.CLOCK: IC9.4, P8.28, R34.1
LCD.D0.B0--B3: C42.1, IC1.R1, IC9.15, P8.45, R87.2
LCD.D1.B1--B4: C41.1, IC1.R2, IC9.13, P8.46, R85.2
LCD.D2.B2--B5: C40.1, IC1.R3, IC9.12, P8.43, R82.1, R88.1
LCD.D3.B3--B6: C39.1, IC1.R4, IC9.11, P8.44, R80.1
LCD.D4.B4--B7: C38.1, IC1.T1, IC9.10, P8.41, R78.1
LCD.D5.G0--G2: C37.1, IC1.T2, IC9.7, P8.42, R76.1
LCD.D6.G1--G3: C36.1, IC1.T3, IC9.6, P8.39, R75.2
LCD.D7.G2--G4: C35.1, IC1.T4, IC9.3, P8.40, R73.2
LCD.D8.G3--G5: C34.1, IC1.U1, IC9.2, P8.37, R71.2
LCD.D9.G4--G6: C33.1, IC1.U2, IC9.1, P8.38, R69.2
LCD.D10.G5--G7: C32.1, IC1.U3, IC9.64, P8.36, R67.2
LCD.D11.R0--R3: C31.1, IC1.U4, IC9.60, P8.34, R65.2
LCD.D12.R1--R4: C30.1, IC1.V2, IC9.59, P8.35, R63.2
LCD.D13.R2--R5: C29.1, IC1.V3, IC9.58, P8.33, R61.2
LCD.D14.R3--R6: C28.1, IC1.V4, IC9.57, P8.31, R58.1
LCD.D15.R4--R7: C27.1, IC1.T5, IC9.56, P8.32, R57.2
LCD.ENABLE: IC9.20, P8.30, R39.1
LCD.HSYNC: IC9.22, P8.29, R37.1
LCD.VSYNC: IC9.21, P8.27, R35.1
LDO_PGOOD: IC1.B5, IC1.B20
LS_BUF_OE: IC1.L18, R131.2
MCU.LCD.CLK: IC1.V5, R34.2
MCU.LCD.EN: IC1.R6, R39.2
MCU.LCD.HS: IC1.R5, R37.2
MCU.LCD.VS: IC1.U5, R35.2
MMC1_CLK: IC1.U9, IC22.M6, P8.21, R31.1
MMC1_CMD: IC1.V9, IC22.M5, P8.20, R30.1
MMC1_DAT0: IC1.U7, IC22.A3, P8.25, R12.1
MMC1_DAT1: IC1.V7, IC22.A4, P8.24, R13.1
MMC1_DAT2: IC1.R8, IC22.A5, P8.5, R16.1
MMC1_DAT3: IC1.T8, IC22.B2, P8.6, R18.1
MMC1_DAT4: IC1.U8, IC22.B3, P8.23, R20.1
MMC1_DAT5: IC1.V8, IC22.B4, P8.22, R23.1
MMC1_DAT6: IC1.R9, IC22.B5, P8.3, R25.1
MMC1_DAT7: IC1.T9, IC22.B6, P8.4, R28.1
unnamed: OSC2.1, R90.2
unnamed: R88.2, S2.1, S2.2
unnamed: FB5.1, IC1.A15
unnamed: PWR.K, R55.2
unnamed: IC18.1, R89.2, R97.2
unnamed: C4.1, IC1.K20, Q4.1, R8.1
unnamed: C3.1, IC1.M20, Q4.2, R8.2
unnamed: IC1.C6, IC1.D19
unnamed: IC18.5, R93.2, R94.1
unnamed: C3.2, C4.2, IC1.L20
unnamed: C5.2, C6.2, IC1.G20
unnamed: ANT2.SIG, C60.1
unnamed: ANT1.SIG, C46.1
unnamed: C46.2, MOD1.32
unnamed: R100.1, USR1.A
unnamed: R96.1, USR2.A
unnamed: R92.1, USR3.A
unnamed: C60.2, MOD1.18
unnamed: IC1.P17, R27.1
unnamed: IC1.B4, R24.2
unnamed: BT.K, T4.D
unnamed: R125.1, WL.A
unnamed: IC1.D13, R14.2
unnamed: FB7.2, IC1.D14
unnamed: IC1.R14, IC3.2
unnamed: IC3.4, R29.2
unnamed: MOD1.26, TP12.TP
unnamed: R104.1, USR0.A
unnamed: MOD1.27, TP13.TP
unnamed: C5.1, IC1.H20, Q2.P$1, R56.2
unnamed: C6.1, IC1.F20, Q2.P$2, R56.1
unnamed: MOD1.42, TP14.TP
unnamed: MOD1.43, TP15.TP
unnamed: MOD1.56, TP16.TP
unnamed: MOD1.57, TP17.TP
unnamed: OSC1.3, R110.1
unnamed: MOD1.58, TP18.TP
unnamed: MOD1.60, TP19.TP
unnamed: IC1.P15, R26.1
unnamed: C7.1, C69.1, IC22.C2
unnamed: IC1.C18, R36.2
unnamed: IC1.B12, R38.2
unnamed: IC5.2, R44.2, R45.1, T1.B
unnamed: IC5.1, R45.2, R46.2, R47.1
unnamed: IC6.2, R48.2, R49.1, T2.B
unnamed: IC6.1, R49.2, R50.2, R51.1
unnamed: IC4.5, R40.2, TP1.P$1
unnamed: BT.A, R124.1
unnamed: FB6.1, IC13.5
unnamed: MGT1.P$1, MGT2.P$1, MGT3.P$1, MGT4.P$1, R17.2, X2.CGND1, X2.CGND2, X2.CGND3, X2.CGND4, X2.CGND5, X2.CGND6, X3.5, X3.6, X4.CGND1, X4.CGND2, X4.CGND3, X4.CGND4, X4.CGND5, X4.CGND6, X5.CG1, X5.CG2, X5.CG3, X5.CG4
unnamed: MOD1.13, R72.1
unnamed: MOD1.12, R70.1
unnamed: MOD1.11, R68.1
unnamed: MOD1.10, R66.1
unnamed: D1.A, R120.2
unnamed: MOD1.8, R64.1
unnamed: MOD1.6, R62.1
unnamed: MOD1.50, R140.1
unnamed: MOD1.51, R141.1
unnamed: MOD1.52, R142.1
unnamed: MOD1.53, R143.1
unnamed: IC10.14, R86.2
NC3: MOD1.14, R60.1, R111.2
PMIC_INT: IC1.B18, IC1.B19
PMIC_NWAKEUP: IC1.A19, IC1.C5
PMIC_PGOOD: IC1.A20, IC1.B15, IC2.2
PWR_BUT: IC1.D20, P9.9, POWER.3, POWER.4
RX<-TX: IC17.3, X1.5
SD.CD: IC1.C15, P2.19, R7.1, X2.CD
SD.CLK: IC1.G17, R3.1, X2.5
SD.CMD: IC1.G18, R4.1, X2.3
SD.D0: IC1.G16, R2.1, X2.7
SD.D1: IC1.G15, R1.1, X2.8
SD.D2: IC1.F18, R6.1, X2.1
SD.D3: IC1.F17, R5.1, X2.2
SELECT_5V: D2.K, D3.K, D4.K, FB1.1, R97.1, TP23.TP
SLOW_CLK: IC11.5, R91.1
SPI1_CS0: IC1.C12, IC9.25, P9.28
SPI1_D0: IC1.B13, IC9.24, P9.29
SPI1_D1: IC1.D12, P9.30
SPI1_SCLK: IC1.A13, IC9.23, P9.31
SYS_5V: C62.+, D2.A, F1.2, IC1.W4, IC1.Y4, IC12.2, IC12.3, P9.7, P9.8
SYS_RESET#: C16.1, C21.1, IC1.A10, IC2.4, P2.15, P9.10, R32.2, RESET.3, RESET.4
TEST: IC9.49, R114.2
TIMER4: IC1.R7, P8.7
TIMER5: IC1.T6, P8.9
TIMER6: IC1.U6, P8.10
TIMER7: IC1.T7, P8.8
TX0+: IC8.5, IC9.40, X5.9
TX0-: IC8.4, IC9.39, X5.11
TX1+: IC7.2, IC9.43, X5.6
TX1-: IC7.1, IC9.42, X5.8
TX2+: IC7.5, IC9.45, X5.3
TX2-: IC7.4, IC9.44, X5.5
TX->RX: IC17.2, R123.1, X1.4
TXC+: IC8.2, IC9.38, X5.12
TXC-: IC8.1, IC9.37, X5.14
UART0_RST#: IC1.E17, TP6.TP
UART0_RXD: IC1.E15, IC17.6
UART0_TXD: IC1.E16, IC17.5
UART1_RXD: IC1.D16, P9.26
UART1_TXD: IC1.D15, P9.24
UART2_RXD: IC1.A17, P9.22
UART2_TXD: IC1.B17, P9.21
UART4_RXD: IC1.T17, P9.11
UART4_TXD: IC1.U17, P9.13
USB1_DRVVBUS: IC1.F15, IC12.4, R19.1
USB1_OC#: IC1.T16, IC12.5, R122.2
USB1_VBUS: FB4.2, IC1.T18
USB.CLIENT.D+: IC1.N17, IC14.1, X4.D+
USB.CLIENT.D-: IC1.N18, IC14.2, X4.D-
USB.CLIENT.ID: IC1.P16, IC14.3, X4.ID
USB.HOST.D+: IC1.R17, IC15.1, X3.3
USB.HOST.D-: IC1.R18, IC15.2, X3.2
USB_DC: C59.1, D4.A, IC1.Y8, IC1.Y9, IC14.6, R26.2, X4.VBUS
USR0: IC1.V15, R104.2
USR1: IC1.U15, R100.2
USR2: IC1.T15, R96.2
USR3: IC1.V16, R92.2
VBUS.HOST: FB3.2, X3.1
VBUS.OUT: C58.1, FB3.1, FB4.1, IC12.6, IC12.7, IC12.8, IC15.6
VDD_1V8: FB2.1, IC1.D10, IC1.E9, IC1.N16, IC1.R16, IC2.5, IC5.3, IC6.3, R47.2, R51.2, T1.C, T2.C
VDD_3V3A: IC1.N5, IC1.P5, IC1.P6, IC1.P7, R44.1, R46.1, T1.E
VDD_3V3AUX: IC1.Y11, PWR.A
VDD_3V3B: C1.1, C2.1, C9.1, C12.1, C13.1, C14.1, C15.1, C17.1, C18.1, C22.1, C47.1, C48.1, C49.1, IC1.U20, IC1.V20, IC3.5, IC4.4, IC13.6, IC13.7, IC13.8, IC17.7, IC17.8, IC22.C6, IC22.E6, IC22.F5, IC22.J10, IC22.K9, IC22.M4, IC22.N4, IC22.P3, IC22.P5, OSC1.4, P2.5, P9.3, P9.4, R1.2, R2.2, R3.2, R4.2, R5.2, R6.2, R7.2, R12.2, R13.2, R16.2, R18.2, R20.2, R21.1, R23.2, R25.2, R28.2, R30.2, R31.2, R32.1, R33.2, R40.1, R41.1, R42.1, R43.1, R48.1, R50.1, R53.1, R58.2, R76.2, R78.2, R80.2, R82.2, R89.1, R120.1, R121.1, R122.1, T2.E, X2.4
VDD_5V: D3.A, IC1.Y5, IC1.Y6, P9.5, P9.6, X12.IN
VDD_ADC: IC1.A4, IC1.A5, IC1.B9, IC1.D8, P9.32
VIN_BAT: IC1.Y2, IC1.Y3, TP2.P$1
WL_EN: IC11.3, MOD1.40, R10.1, T3.G
WL_EN.SIP: IC1.K18, R136.1
WL_IRQ: IC11.9, R60.2
WL_IRQ.SIP: IC1.H18, R134.1
WL_SDIO_CLK: IC10.6, R64.2, R103.2
WL_SDIO_CLK.SIP: IC1.L15, R126.1
WL_SDIO_CMD: IC10.7, R62.2, R105.2
WL_SDIO_CMD.SIP: IC1.J16, R86.1
WL_SDIO_D0: IC10.1, R66.2, R98.2
WL_SDIO_D0.SIP: IC1.J17, R130.1
WL_SDIO_D1: IC10.3, R68.2, R99.2
WL_SDIO_D1.SIP: IC1.J18, R129.1
WL_SDIO_D2: IC10.4, R70.2, R101.2
WL_SDIO_D2.SIP: IC1.K15, R128.1
WL_SDIO_D3: IC10.5, R72.2, R102.2
WL_SDIO_D3.SIP: IC1.H16, R127.1
XDMA_EVENT_INTRO: FB5.2, IC13.1, P2.17
